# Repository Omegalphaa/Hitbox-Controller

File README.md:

# Hitbox-Controller
2 PCB designs for Hitbox style controllers mint for traditional fighting games.

The Cherry/Gateron design is made to have 30mm circular keycaps for all the buttons execept the left, down, and right buttons they are made for a 24mm buttons. These can be made in whatever preference you may like. 

The Kailh design is made to have a 24mm circular keycaps for all of the buttons execept the up button it was designed for a pill shaped keycap to be accessable to both hands.

Both designs require a Brook UFB and optionally the Brook UFB UP-5 for Playstation 5 support.

In this repository you will be able to find both the Kicad files and the already prepared gerber files to send it to a PCB manufaturer of your choice to get these made.

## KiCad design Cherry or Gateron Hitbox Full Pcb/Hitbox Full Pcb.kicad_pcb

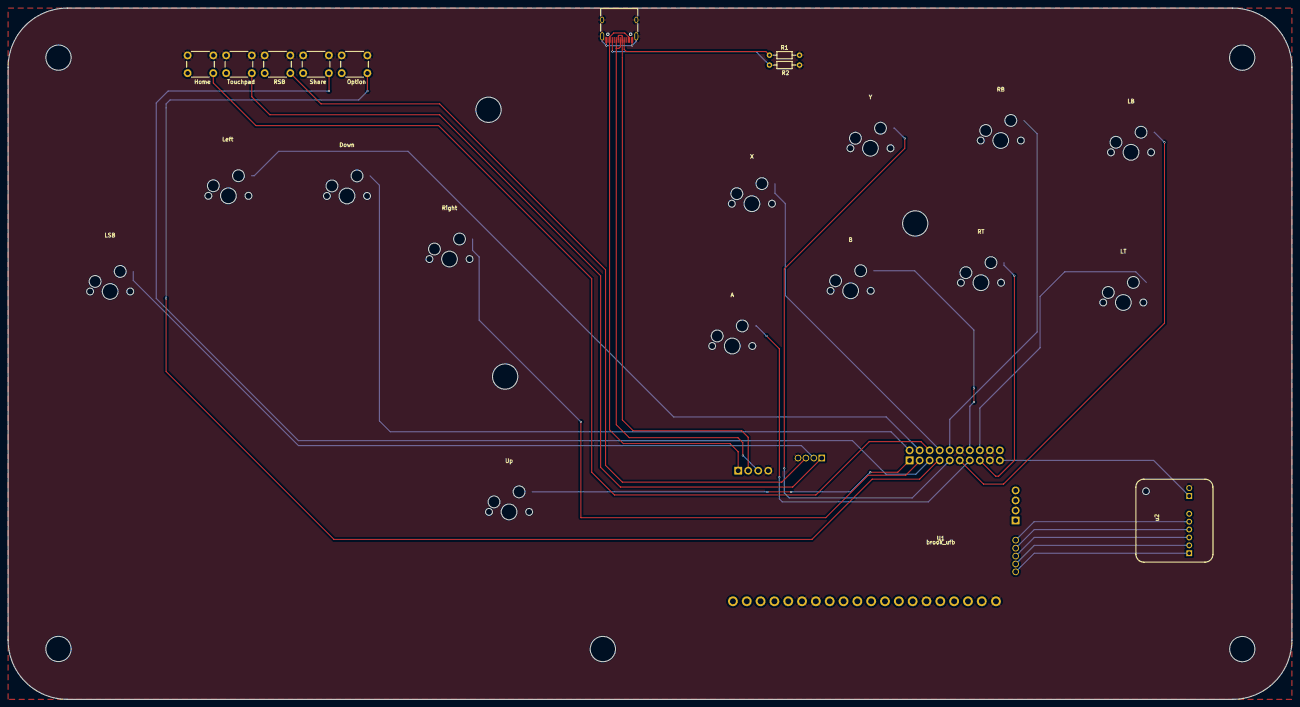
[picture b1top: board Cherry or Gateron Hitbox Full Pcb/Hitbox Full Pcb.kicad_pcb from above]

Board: 2 copper layers, 325.0 x 175.0 mm, 23 parts (0 on the bottom side), 30 nets.

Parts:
MX1: LSB; MXOnly-1U-Hotswap
MX2: Left; MXOnly-1U-Hotswap
MX3: Down; MXOnly-1U-Hotswap
MX4: Right; MXOnly-1U-Hotswap
MX5: Up; MXOnly-1U-Hotswap
MX6: X; MXOnly-1U-Hotswap
MX7: Y; MXOnly-1U-Hotswap
MX8: RB; MXOnly-1U-Hotswap
MX9: LB; MXOnly-1U-Hotswap
MX10: A; MXOnly-1U-Hotswap
MX11: B; MXOnly-1U-Hotswap
MX12: RT; MXOnly-1U-Hotswap
MX13: LT; MXOnly-1U-Hotswap
R1, R2: 5.1k; R_Axial_DIN0204_L3.6mm_D1.6mm_P7.62mm_Horizontal
SW1: Home; SW_PUSH_6mm_H8.5mm
SW2: Touchpad; SW_PUSH_6mm_H8.5mm
SW3: RSB; SW_PUSH_6mm_H8.5mm
SW4: Share; SW_PUSH_6mm_H8.5mm
SW5: Option; SW_PUSH_6mm_H8.5mm
U1: brook_ufb; Brook_Universal_Fighting_Board
USB1: HRO-TYPE-C-31-M-12; USB_C_Receptacle_HRO_TYPE-C-31-M-12
u2: brook_ufb-up5; UFB-UP5

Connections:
GND: MX1.1 (COL), MX2.1 (COL), MX3.1 (COL), MX4.1 (COL), MX5.1 (COL), MX6.1 (COL), MX7.1 (COL), MX8.1 (COL), MX9.1 (COL), MX10.1 (COL), MX11.1 (COL), MX12.1 (COL), MX13.1 (COL), R1.2, R2.2, SW1.1, SW2.1, SW3.1, SW4.1, SW5.1, U1.3 (J9_19_GND), U1.4 (J9_20_GND), U1.10 (J9_20_GND), U1.33 (J4_GND), U1.34 (J6-1_GND), U1.38 (J3_GND), U1.43 (J3_GND1), U1.51 (J3_GND2), U1.52 (J3_GND3), USB1.13 (Shield), USB1.A1, USB1.A12 (GND), USB1.B1 (GND), USB1.B12, u2.1 (J1_2)
J2-1: U1.29 (J2_1), u2.8 (J3_1)
J2-2: U1.28 (J2_2), u2.7 (J3_2)
J2-3: U1.27 (J2_3), u2.6 (J3_3)
J2-4: U1.26 (J2_4), u2.5 (J3_4)
J2-5: U1.25 (J2_5), u2.4 (J3_5)
LB: MX9.2 (ROW), U1.9 (J9_19_4P/L1/LB)
LSB: MX1.2 (ROW), U1.31 (J4_LSB)
LT: MX13.2 (ROW), U1.6 (J9_20_4K/L2/LT)
unnamed: R1.1, USB1.A5 (CC1)
unnamed: R2.1, USB1.B5 (CC2)
RB: MX8.2 (ROW), U1.12 (J9_20_3P/R1/RB)
RSB: SW3.2, U1.32 (J4_RSB)
RT: MX12.2 (ROW), U1.5 (J9_19_3K/R2/RT)
Touchpad: SW2.2, U1.30 (J4_TPKEY)
VCC: U1.1 (J9_19_VCC), u2.2 (J1_1)
a: MX10.2 (ROW), U1.7 (J9_19_1K/X/A)
b: MX11.2 (ROW), U1.8 (J9_20_2K/O/B)
d+: U1.35 (J6-1_D+), USB1.A6 (DP1), USB1.B6 (DP2)
d-: U1.36 (J6-1_D-), USB1.A7 (DN1), USB1.B7 (DN2)
down: MX3.2 (ROW), U1.20 (J9_20_DOWN)
home: SW1.2, U1.16 (J9_20_Home/Ps/Xb)
left: MX2.2 (ROW), U1.18 (J9_20_LEFT)
option: SW5.2, U1.13 (J9_19_Start/Options)
right: MX4.2 (ROW), U1.17 (J9_19_RIGHT)
share: SW4.2, U1.15 (J9_19_Select/Share/Back)
up: MX5.2 (ROW), U1.19 (J9_19_UP)
v: U1.37 (J6-1_VCC), USB1.A4 (VBUS), USB1.A9 (VBUS), USB1.B4 (VBUS), USB1.B9 (VBUS)
x: MX6.2 (ROW), U1.14 (J9_20_1P/Square/X)
y: MX7.2 (ROW), U1.11 (J9_19_2P/Triangle/Y)

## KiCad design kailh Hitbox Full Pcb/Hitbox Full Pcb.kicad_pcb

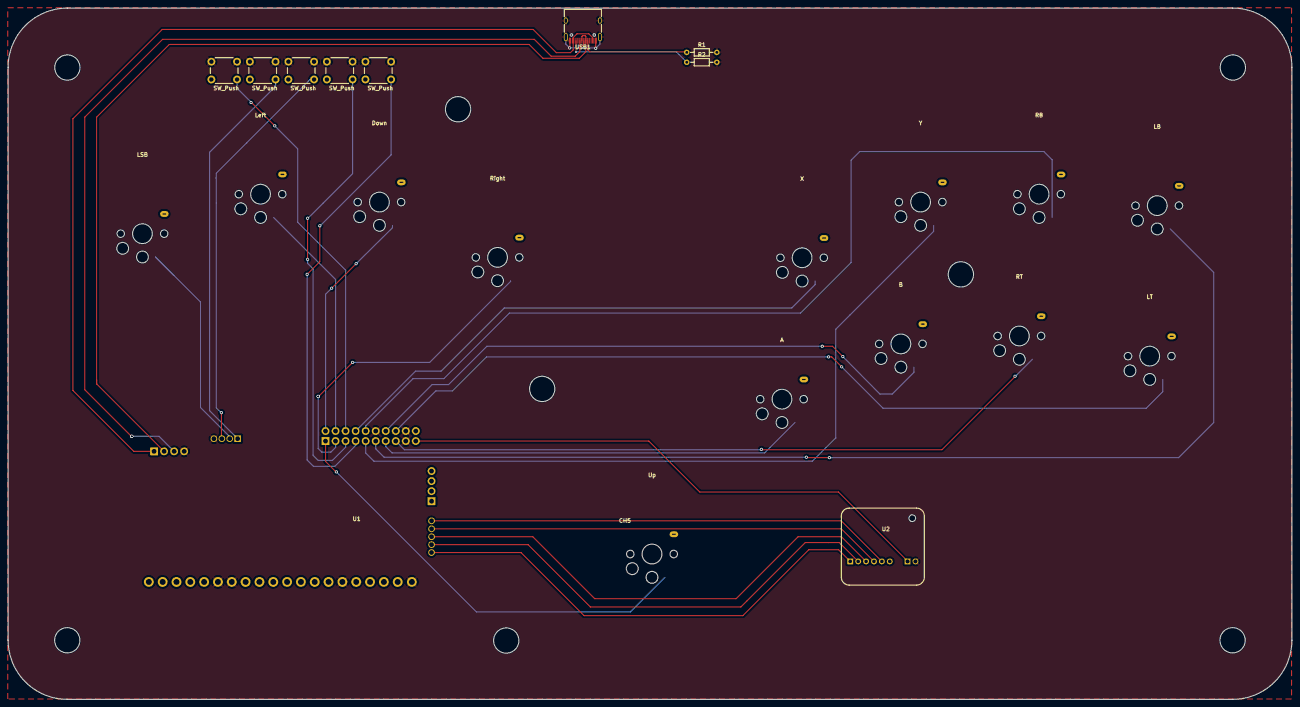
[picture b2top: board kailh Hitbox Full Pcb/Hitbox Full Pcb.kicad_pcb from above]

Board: 2 copper layers, 325.0 x 175.0 mm, 23 parts (0 on the bottom side), 30 nets.

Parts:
CH1, CH2, CH3, CH4, CH5, CH6, CH7, CH8, CH9, CH10, CH11, CH12, CH13: MX-NOLED; ChocV1_V2_Hotswap
R1, R2: 5.1k; R_Axial_DIN0204_L3.6mm_D1.6mm_P7.62mm_Horizontal
SW1, SW2, SW3, SW4, SW5: SW_Push; SW_PUSH_6mm_H8.5mm
U1: brook_ufb; Brook_Universal_Fighting_Board
U2: brook_ufb-up5; UFB-UP5
USB1: HRO-TYPE-C-31-M-12; USB_C_Receptacle_HRO_TYPE-C-31-M-12

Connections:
GND: CH1.1 (COL), CH2.1 (COL), CH3.1 (COL), CH4.1 (COL), CH5.1 (COL), CH6.1 (COL), CH7.1 (COL), CH8.1 (COL), CH9.1 (COL), CH10.1 (COL), CH11.1 (COL), CH12.1 (COL), CH13.1 (COL), R1.2, R2.2, SW1.1, SW2.1, SW3.1, SW4.1, SW5.1, U1.3 (J9_19_GND), U1.4 (J9_20_GND), U1.10 (J9_20_GND), U1.33 (J4_GND), U1.34 (J6-1_GND), U1.38 (J3_GND), U1.43 (J3_GND1), U1.51 (J3_GND2), U1.52 (J3_GND3), U2.1 (J1_2), USB1.13 (Shield), USB1.A1 (GND), USB1.A12 (GND), USB1.B1 (GND), USB1.B12 (GND)
J2-1: U1.29 (J2_1), U2.8 (J3_1)
J2-2: U1.28 (J2_2), U2.7 (J3_2)
J2-3: U1.27 (J2_3), U2.6 (J3_3)
J2-4: U1.26 (J2_4), U2.5 (J3_4)
J2-5: U1.25 (J2_5), U2.4 (J3_5)
LB: CH9.2 (ROW), U1.9 (J9_19_4P/L1/LB)
LSB: CH1.2 (ROW), U1.31 (J4_LSB)
LT: CH13.2 (ROW), U1.6 (J9_20_4K/L2/LT)
unnamed: R1.1, USB1.A5 (CC1)
unnamed: R2.1, USB1.B5 (CC2)
RB: CH8.2 (ROW), U1.12 (J9_20_3P/R1/RB)
RSB: SW3.2, U1.32 (J4_RSB)
RT: CH12.2 (ROW), U1.5 (J9_19_3K/R2/RT)
Touchpad: SW2.2, U1.30 (J4_TPKEY)
VCC: U1.1 (J9_19_VCC), U2.2 (J1_1)
a: CH10.2 (ROW), U1.7 (J9_19_1K/X/A)
b: CH11.2 (ROW), U1.8 (J9_20_2K/O/B)
d+: U1.35 (J6-1_D+), USB1.A6 (DP1), USB1.B6 (DP2)
d-: U1.36 (J6-1_D-), USB1.A7 (DN1), USB1.B7 (DN2)
down: CH3.2 (ROW), U1.20 (J9_20_DOWN)
home: SW1.2, U1.16 (J9_20_Home/Ps/Xb)
left: CH2.2 (ROW), U1.18 (J9_20_LEFT)
option: SW5.2, U1.13 (J9_19_Start/Options)
right: CH4.2 (ROW), U1.17 (J9_19_RIGHT)
share: SW4.2, U1.15 (J9_19_Select/Share/Back)
up: CH5.2 (ROW), U1.19 (J9_19_UP)
v: U1.37 (J6-1_VCC), USB1.A4 (VBUS), USB1.A9 (VBUS), USB1.B4 (VBUS), USB1.B9 (VBUS)
x: CH6.2 (ROW), U1.14 (J9_20_1P/Square/X)
y: CH7.2 (ROW), U1.11 (J9_19_2P/Triangle/Y)

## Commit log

2024-05-10 Renaming
